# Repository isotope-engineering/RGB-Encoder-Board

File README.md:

# RGB Rotary Encoder

## What is this?
This is a super-overkill rotary encoder. Not only does it encode in a rotary fashion, it also lights up! It includes a ring of 20 ultra bright and even more ultra tiny Neopixel LEDs. Ever have trouble deciding between different LED colors? Well here you don't have to. Add this to your next project to give it a brilliant flare in whatever color, or combination of colors, you want.

## How do I use it?
Check out the example code in this repo. The provided examples are for use with a Teensy, but it can be used with any controller that can run Neopixels and read an encoder.

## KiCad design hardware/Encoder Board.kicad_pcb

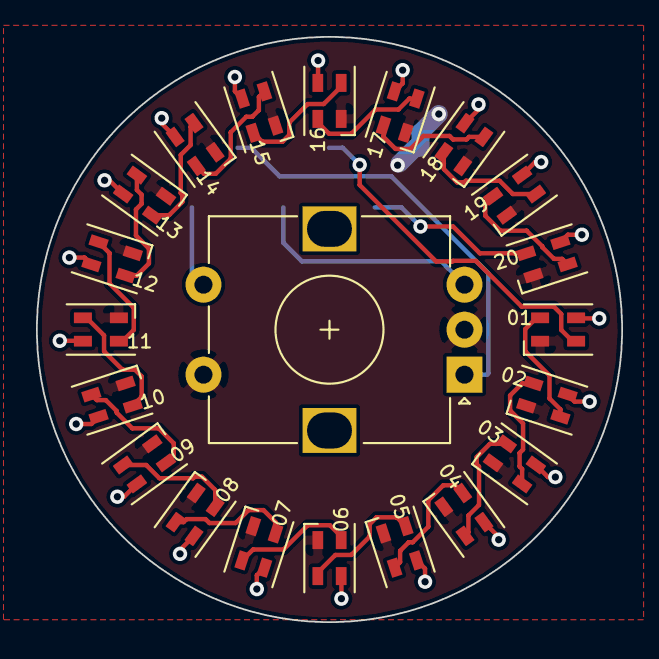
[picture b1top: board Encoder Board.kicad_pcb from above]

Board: 2 copper layers, 32.5 x 32.5 mm, 22 parts (1 on the bottom side), 26 nets.

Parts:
D1, D2, D3, D4, D5, D6, D7, D8, D9, D10, D11, D12, D13, D14, D15, D16, D17, D18, D19, D20: SK6805; LED_SK6805_PLCC4_2.4x2.7mm_P1.3mm
J1: Conn_01x08_Female; PinHeader_1x07_P2.54mm_Vertical_SMD_Pin1Left
SW1: Rotary_Encoder_Switch; RotaryEncoder_Alps_EC12E-Switch_Vertical_H20mm

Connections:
+5V: D1.4, D2.4, D3.4, D4.4, D5.4, D6.4, D7.4, D8.4, D9.4, D10.4, D11.4, D12.4, D13.4, D14.4, D15.4, D16.4, D17.4, D18.4, D19.4, D20.4, J1.1
DIN: D1.3, J1.4
DOUT: D20.1, J1.3
ENC_A: J1.6, SW1.A
ENC_B: J1.5, SW1.B
GND: D1.2, D2.2, D3.2, D4.2, D5.2, D6.2, D7.2, D8.2, D9.2, D10.2, D11.2, D12.2, D13.2, D14.2, D15.2, D16.2, D17.2, D18.2, D19.2, D20.2, J1.2, SW1.C, SW1.S1
unnamed: D1.1, D2.3
unnamed: D2.1, D3.3
unnamed: D3.1, D4.3
unnamed: D4.1, D5.3
unnamed: D5.1, D6.3
unnamed: D6.1, D7.3
unnamed: D7.1, D8.3
unnamed: D8.1, D9.3
unnamed: D10.1, D11.3
unnamed: D9.1, D10.3
unnamed: D11.1, D12.3
unnamed: D12.1, D13.3
unnamed: D13.1, D14.3
unnamed: D14.1, D15.3
unnamed: D15.1, D16.3
unnamed: D16.1, D17.3
unnamed: D17.1, D18.3
unnamed: D18.1, D19.3
unnamed: D19.1, D20.3
SW_A: J1.7, SW1.S2

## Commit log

2019-07-14 Readme updates
2019-08-14 Pushed all the stuff
